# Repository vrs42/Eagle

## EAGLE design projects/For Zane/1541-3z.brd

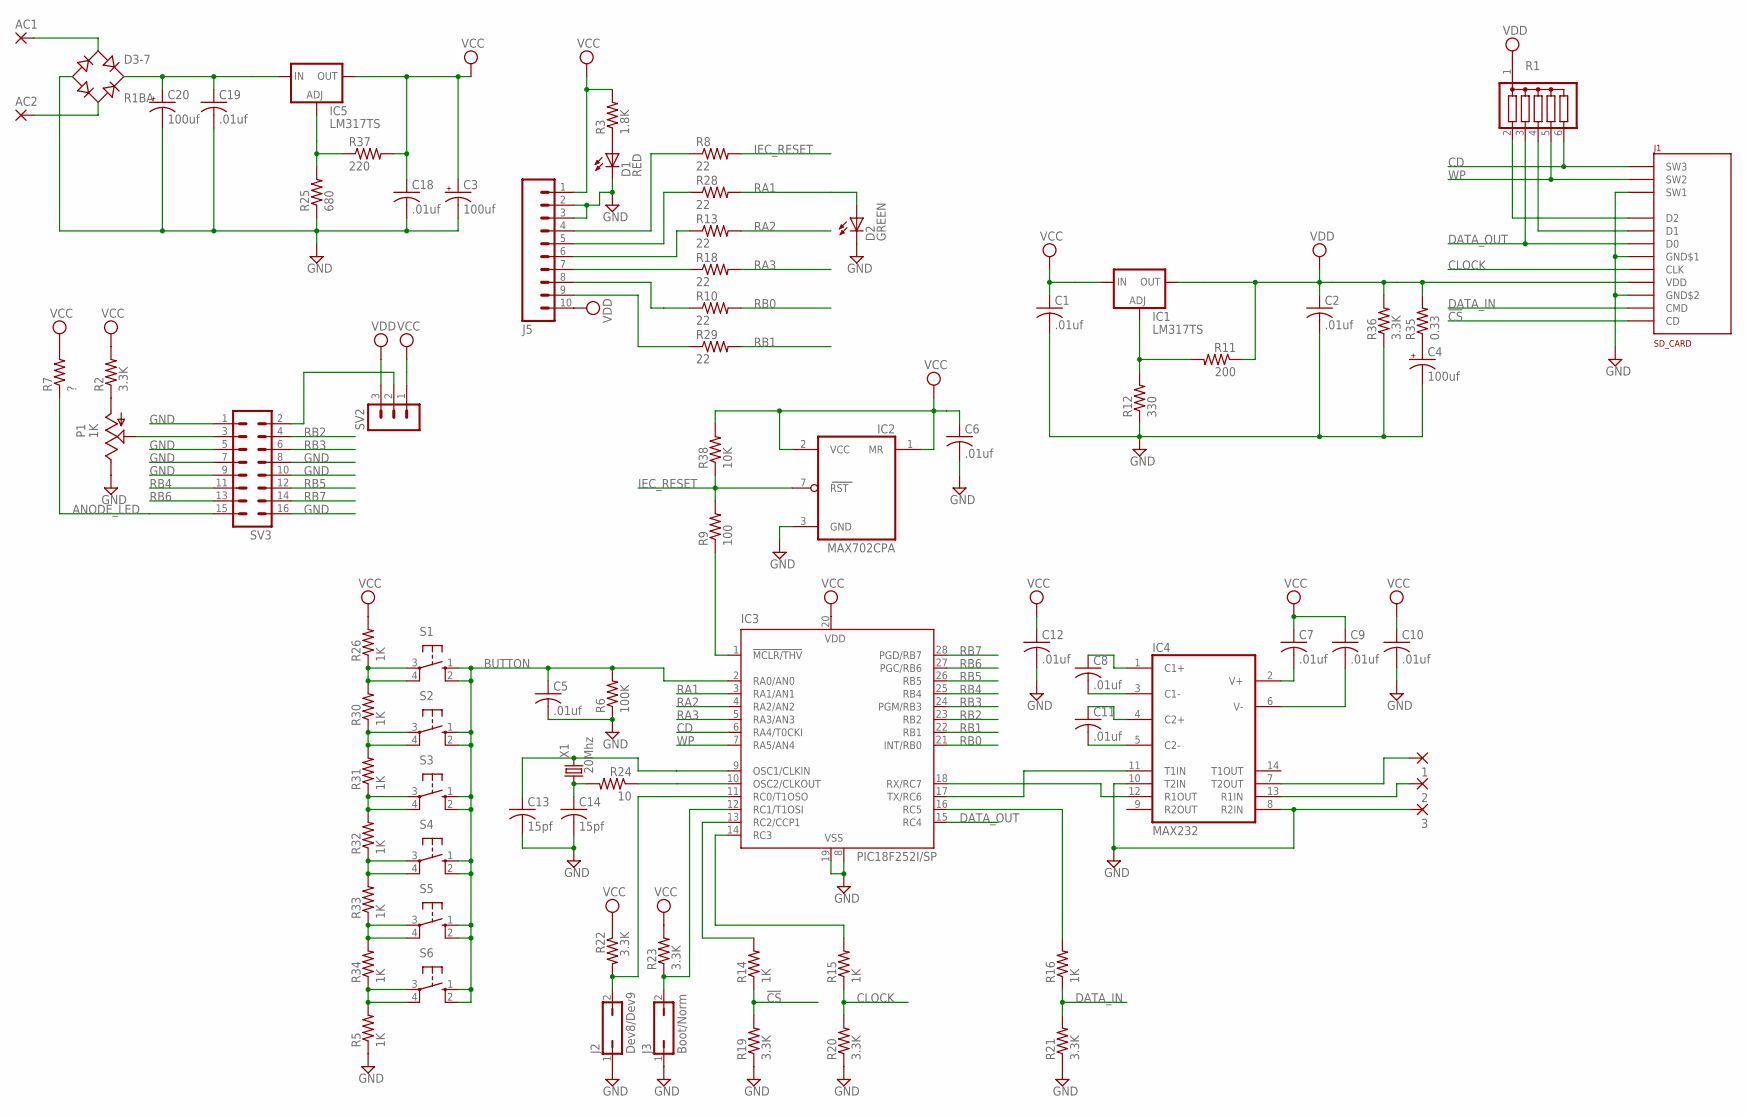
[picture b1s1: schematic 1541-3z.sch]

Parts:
1, 2, 3: 2,15/1,0
AC1, AC2: 2,15/1,0
C1, C2, C5, C6, C7, C8, C9, C10, C11, C12, C18, C19: .01uf; C025-024X044
C3, C4, C20: 100uf; E2-5
C13, C14: 15pf; C025-024X044
D1: RED; LED3MM
D2: GREEN; LED3MM
D3-7: R1BA; RB1A
IC1, IC5: LM317TS; 317TS
IC2: MAX702CPA; DIL08
IC3: PIC18F252I/SP; DIL28-3
IC4: MAX232; DIL16
J1: SD_CARD
J2: Dev8/Dev9; JP1
J3: Boot/Norm; JP1
J5: M10; 10P
P1: 1K; LI10
R1: G05R; SIL6
R2, R19, R20, R21, R22, R23, R36: 3.3K; 0207/2V
R3: 1.8K; 0207/2V
R5, R14, R15, R16, R26, R30, R31, R32, R33, R34: 1K; 0207/2V
R6: 100K; 0207/2V
R7: ?; 0207/2V
R8, R10, R13, R18, R28, R29: 22; 0207/2V
R9: 100; 0207/2V
R11: 200; 0207/2V
R12: 330; 0207/2V
R24: 10; 0207/2V
R25: 680; 0207/2V
R35: 0.33; 0207/2V
R37: 220; 0207/2V
R38: 10K; 0207/2V
S1, S2, S3, S4, S5, S6: 10-XX; B3F-10XX
SV2: MA03-1
SV3: ML16
X1: 20Mhz; HC49U70

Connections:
!CS: J1.DAT3 (CD), R14.1, R19.2
ANODE_LED: R7.1, SV3.15
BUTTON: C5.1, IC3.2 (RA0/AN0), R6.2, S1.1 (S), S1.2 (S1), S2.1 (S), S2.2 (S1), S3.1 (S), S3.2 (S1), S4.1 (S), S4.2 (S1), S5.1 (S), S5.2 (S1), S6.1 (S), S6.2 (S1)
CD: IC3.6 (RA4/T0CKI), J1.SW3, R1.6
CLOCK: J1.CLK, R15.1, R20.2
DATA_IN: J1.CMD, R16.1, R21.2
DATA_OUT: IC3.15 (RC4), J1.DAT0 (D0), R1.3
GND: 3.1, C1.2, C2.2, C3.-, C4.-, C5.2, C6.2, C10.2, C12.2, C13.2, C14.2, C18.2, C19.2, C20.-, D1.K (C), D2.K (C), D3-7.-, IC2.3 (GND), IC3.8 (VSS), IC3.19 (VSS), IC4.8 (R2IN), IC4.10 (T2IN), IC4.15 (GND), J1.SW1, J1.VSS$1 (GND$1), J1.VSS$2 (GND$2), J2.1, J3.1, J5.2, J5.3, P1.E, R5.1, R6.1, R12.1, R19.1, R20.1, R21.1, R25.1, R36.1, SV3.1, SV3.5, SV3.7, SV3.8, SV3.9, SV3.10, SV3.16
IEC_RESET: IC2.7 (RST), R8.2, R9.2, R38.1
unnamed: C4.+, R35.1
unnamed: J1.DAT2 (D2), R1.2
unnamed: J1.DAT1 (D1), R1.4
unnamed: J5.9, R29.1
unnamed: J5.8, R10.1
unnamed: J5.7, R18.1
unnamed: J5.4, R8.1
unnamed: J5.5, R28.1
unnamed: J5.6, R13.1
unnamed: D1.A, R3.1
unnamed: IC3.18 (RX/RC7), IC4.12 (R1OUT)
unnamed: IC3.14 (RC3), R15.2
unnamed: C14.1, R24.2, X1.1
unnamed: IC3.1 (!MCLR/THV), R9.1
unnamed: C11.1, IC4.4 (C2+)
unnamed: C11.2, IC4.5 (C2-)
unnamed: C8.2, IC4.3 (C1-)
unnamed: C8.1, IC4.1 (C1+)
unnamed: C7.2, IC4.2 (V+)
unnamed: C13.1, IC3.9 (OSC1/CLKIN), X1.2
unnamed: IC3.10 (OSC2/CLKOUT), R24.1
unnamed: IC3.12 (RC1/T1OSI), J3.2, R23.1
unnamed: IC3.11 (RC0/T1OSO), J2.2, R22.2
unnamed: IC3.13 (RC2/CCP1), R14.2
unnamed: IC3.16 (RC5), R16.2
unnamed: IC1.1 (ADJ), R11.2, R12.2
unnamed: IC3.17 (TX/RC6), IC4.11 (T1IN)
unnamed: R26.1, R30.2, S1.3, S1.4 (P1)
unnamed: R30.1, R31.2, S2.3, S2.4 (P1)
unnamed: R31.1, R32.2, S3.3, S3.4 (P1)
unnamed: R5.2, R34.1, S6.3, S6.4 (P1)
unnamed: R33.1, R34.2, S5.3, S5.4 (P1)
unnamed: R32.1, R33.2, S4.3, S4.4 (P1)
unnamed: P1.A, R2.1
unnamed: SV2.2, SV3.2
unnamed: P1.S, SV3.3
unnamed: C9.2, IC4.6 (V-)
unnamed: IC5.1 (ADJ), R25.2, R37.1
unnamed: AC1.1, D3-7.AC1
unnamed: C19.1, C20.+, D3-7.+, IC5.3 (IN)
unnamed: AC2.1, D3-7.AC2
unnamed: 2.1, IC4.13 (R1IN)
unnamed: 1.1, IC4.7 (T2OUT)
RA1: D2.A, IC3.3 (RA1/AN1), R28.2
RA2: IC3.4 (RA2/AN2), R13.2
RA3: IC3.5 (RA3/AN3), R18.2
RB0: IC3.21 (INT/RB0), R10.2
RB1: IC3.22 (RB1), R29.2
RB2: IC3.23 (RB2), SV3.4
RB3: IC3.24 (PGM/RB3), SV3.6
RB4: IC3.25 (RB4), SV3.11
RB5: IC3.26 (RB5), SV3.12
RB6: IC3.27 (PGC/RB6), SV3.13
RB7: IC3.28 (PGD/RB7), SV3.14
VCC: C1.1, C3.+, C6.1, C7.1, C9.1, C10.1, C12.1, C18.1, IC1.3 (IN), IC2.1 (MR), IC2.2 (VCC), IC3.20 (VDD), IC4.16 (VCC), IC5.2 (OUT), J5.1, R2.2, R3.2, R7.2, R22.1, R23.2, R26.2, R37.2, R38.2, SV2.1
VDD: C2.1, IC1.2 (OUT), J1.VDD, J5.10, R1.1, R11.1, R35.2, R36.2, SV2.3
WP: IC3.7 (RA5/AN4), J1.SW2, R1.5

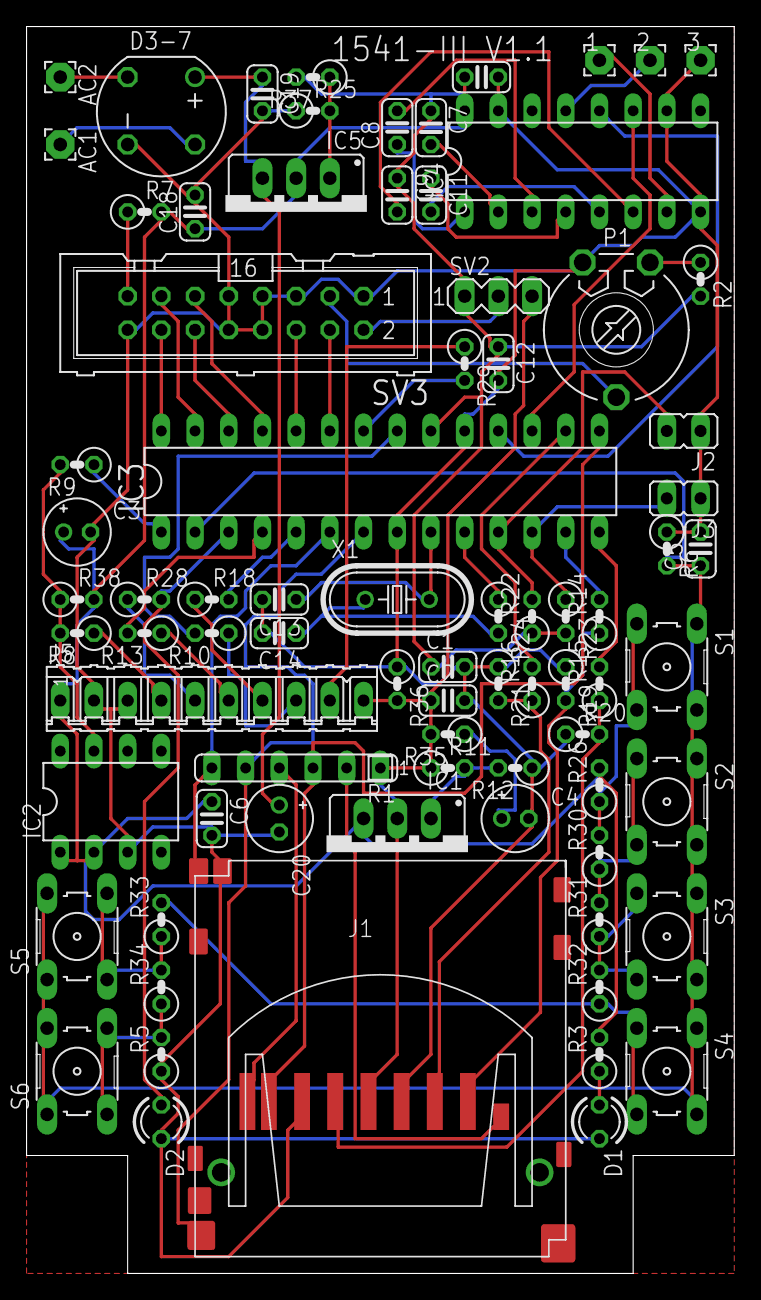
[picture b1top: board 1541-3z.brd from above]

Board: 2 copper layers, 53.3 x 94.0 mm, 79 parts (0 on the bottom side), 66 nets.

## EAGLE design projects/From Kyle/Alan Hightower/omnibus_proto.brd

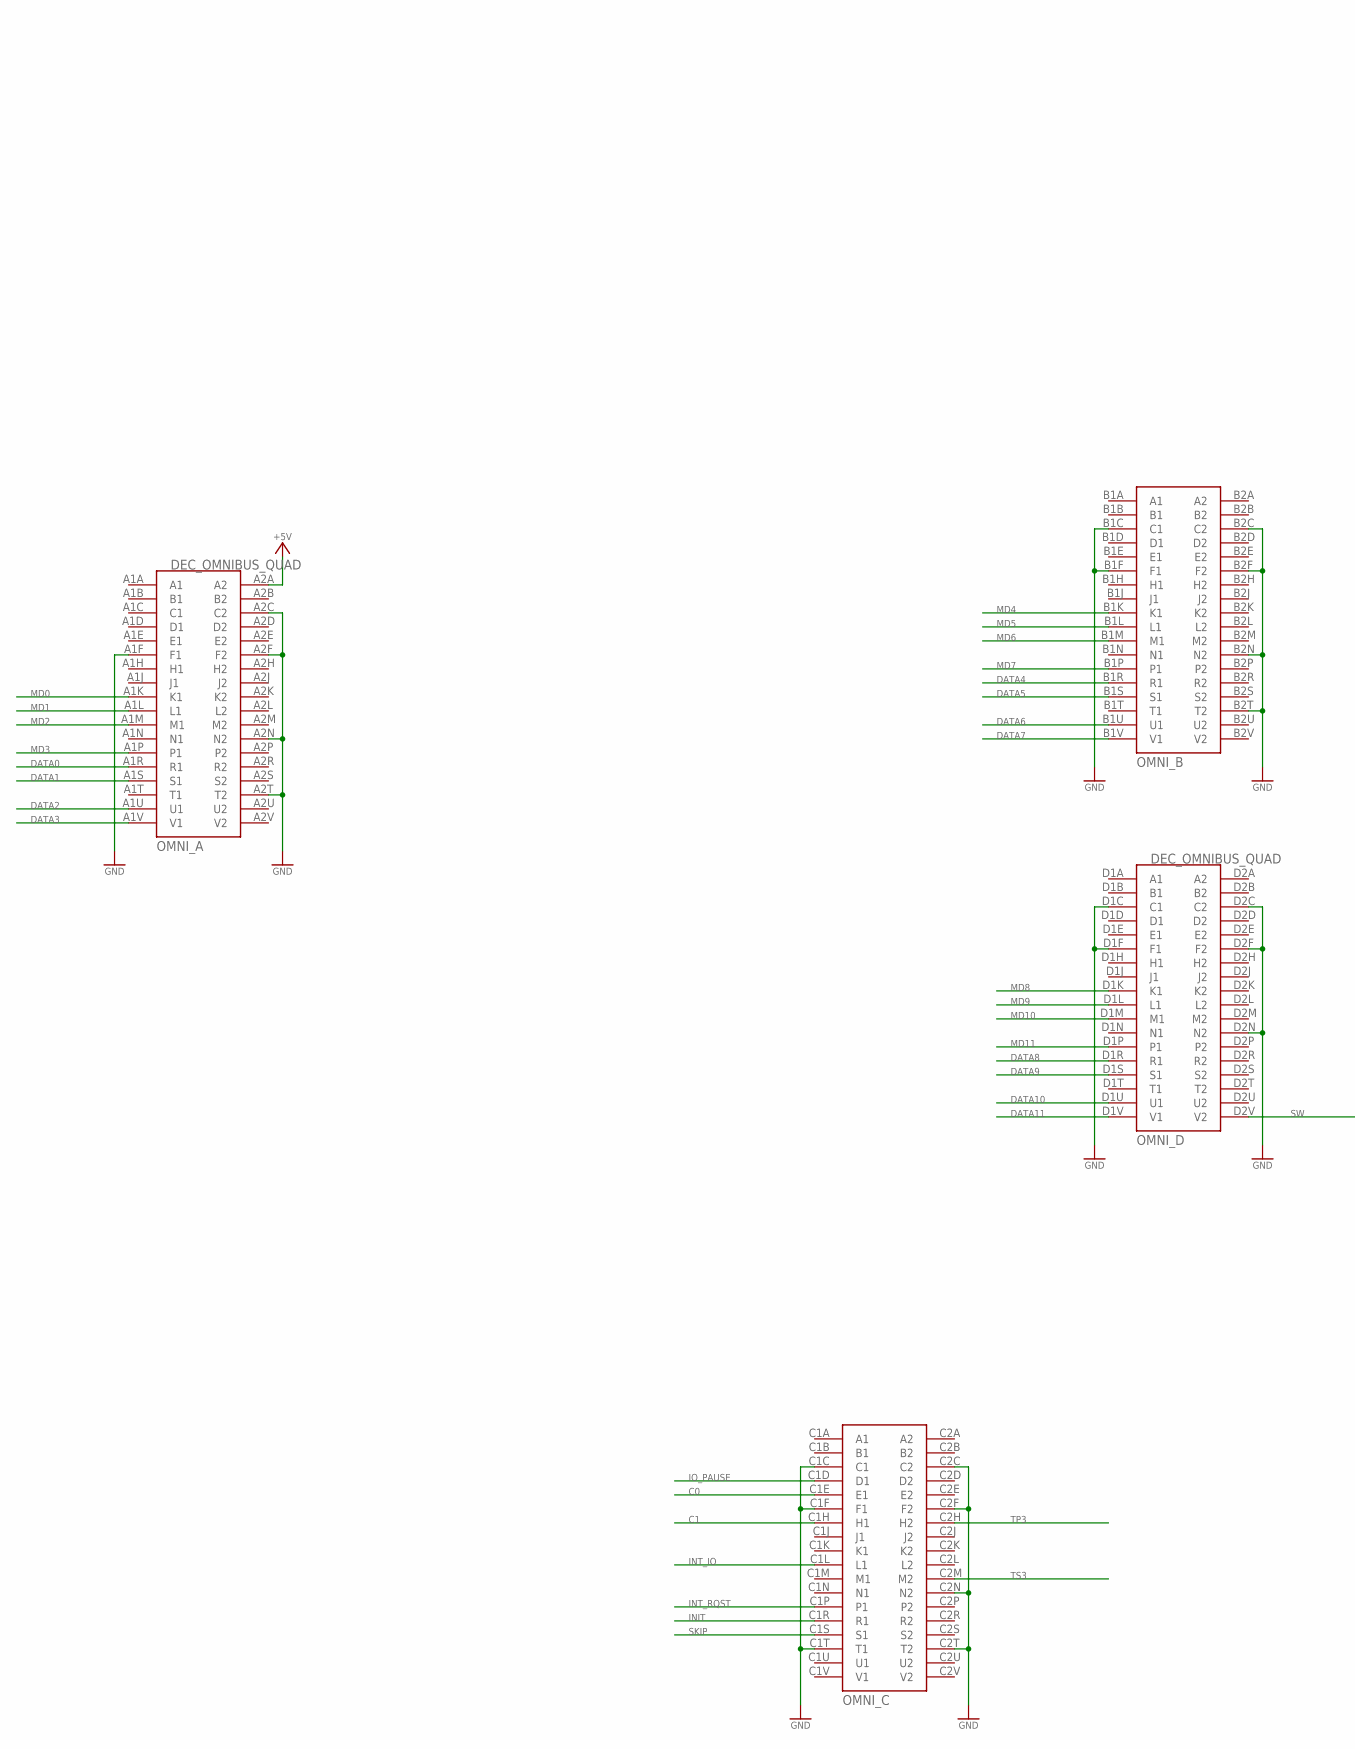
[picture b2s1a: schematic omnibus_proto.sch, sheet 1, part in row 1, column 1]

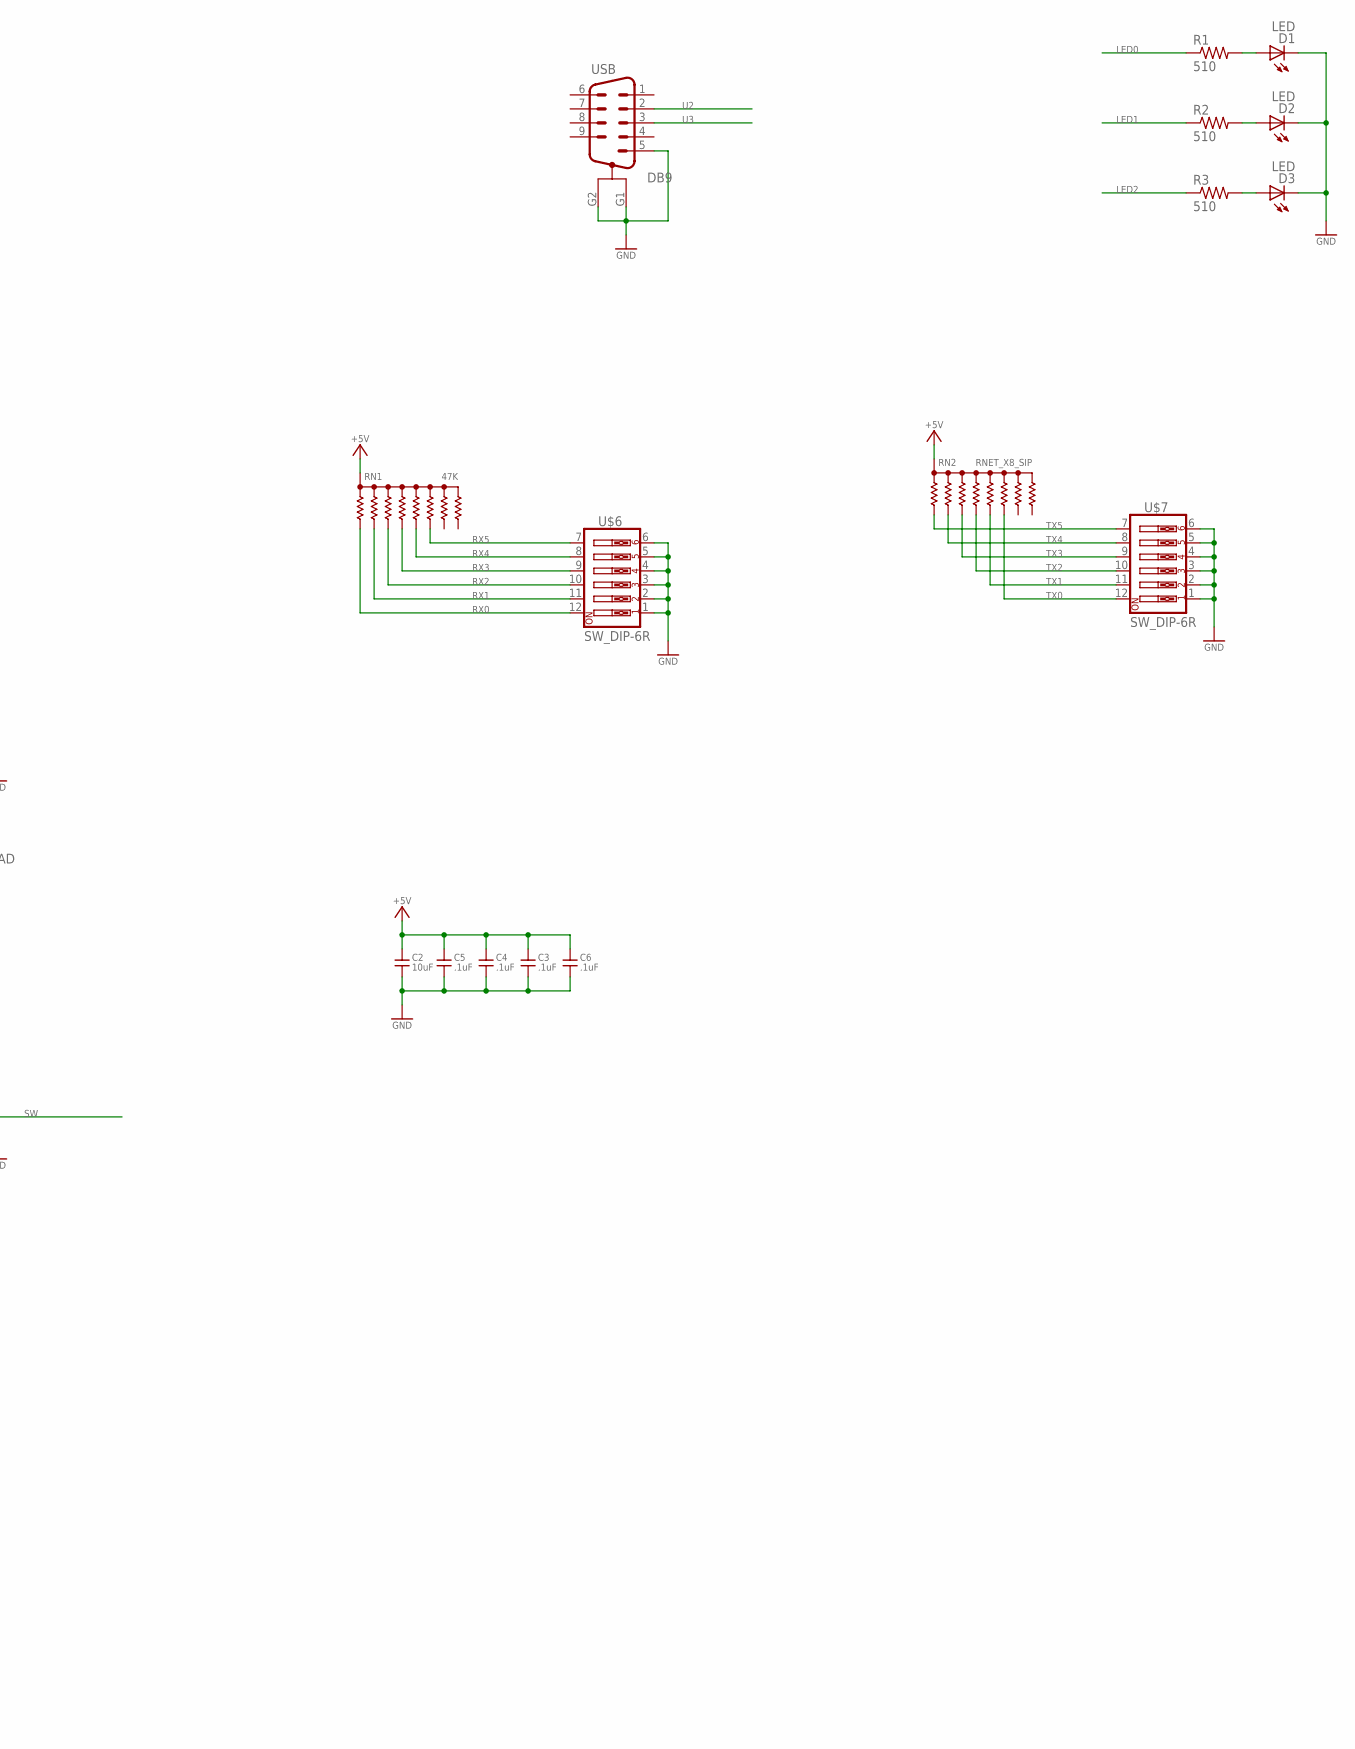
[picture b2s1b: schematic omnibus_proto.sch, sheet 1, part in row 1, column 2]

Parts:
C2: 10uF; C_TH_5MM
C3, C4, C5, C6: .1uF; C_TH_5MM
D1, D2, D3: LED; LED_TH_3MM
OMNI: DEC_OMNIBUS_QUAD
R1, R2, R3: 510; R_204/7
RN1: 47K; RN_SIP9
RN2: RNET_X8_SIP; RN_SIP9
U$6, U$7: SW_DIP-6R; SW_DIP-6_ROUND
USB: DB9; AMP_DB-9RA

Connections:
+5V: C2.1, C3.1, C4.1, C5.1, C6.1, OMNI.A2A (A2), RN1.1, RN2.1; also elsewhere on the board
C0: OMNI.C1E (E1); also elsewhere on the board
C1: OMNI.C1H (H1); also elsewhere on the board
DATA0: OMNI.A1R (R1); also elsewhere on the board
DATA1: OMNI.A1S (S1); also elsewhere on the board
DATA2: OMNI.A1U (U1); also elsewhere on the board
DATA3: OMNI.A1V (V1); also elsewhere on the board
DATA4: OMNI.B1R (R1); also elsewhere on the board
DATA5: OMNI.B1S (S1); also elsewhere on the board
DATA6: OMNI.B1U (U1); also elsewhere on the board
DATA7: OMNI.B1V (V1); also elsewhere on the board
DATA8: OMNI.D1R (R1); also elsewhere on the board
DATA9: OMNI.D1S (S1); also elsewhere on the board
DATA10: OMNI.D1U (U1); also elsewhere on the board
DATA11: OMNI.D1V (V1); also elsewhere on the board
GND: C2.2, C3.2, C4.2, C5.2, C6.2, D1.K (C), D2.K (C), D3.K (C), OMNI.A1F (F1), OMNI.A2C (C2), OMNI.A2F (F2), OMNI.A2N (N2), OMNI.A2T (T2), OMNI.B1C (C1), OMNI.B1F (F1), OMNI.B2C (C2), OMNI.B2F (F2), OMNI.B2N (N2), OMNI.B2T (T2), OMNI.C1C (C1), OMNI.C1F (F1), OMNI.C1T (T1), OMNI.C2C (C2), OMNI.C2F (F2), OMNI.C2N (N2), OMNI.C2T (T2), OMNI.D1C (C1), OMNI.D1F (F1), OMNI.D2C (C2), OMNI.D2F (F2), OMNI.D2N (N2), U$6.1, U$6.2, U$6.3, U$6.4, U$6.5, U$6.6, U$7.1, U$7.2, U$7.3, U$7.4, U$7.5, U$7.6, USB.5, USB.G1, USB.G2; also elsewhere on the board
INIT: OMNI.C1R (R1); also elsewhere on the board
INT_IO: OMNI.C1L (L1); also elsewhere on the board
INT_RQST: OMNI.C1P (P1); also elsewhere on the board
IO_PAUSE: OMNI.C1D (D1); also elsewhere on the board
LED0: R1.1; also elsewhere on the board
LED1: R2.1; also elsewhere on the board
LED2: R3.1; also elsewhere on the board
MD0: OMNI.A1K (K1); also elsewhere on the board
MD1: OMNI.A1L (L1); also elsewhere on the board
MD2: OMNI.A1M (M1); also elsewhere on the board
MD3: OMNI.A1P (P1); also elsewhere on the board
MD4: OMNI.B1K (K1); also elsewhere on the board
MD5: OMNI.B1L (L1); also elsewhere on the board
MD6: OMNI.B1M (M1); also elsewhere on the board
MD7: OMNI.B1P (P1); also elsewhere on the board
MD8: OMNI.D1K (K1); also elsewhere on the board
MD9: OMNI.D1L (L1); also elsewhere on the board
MD10: OMNI.D1M (M1); also elsewhere on the board
MD11: OMNI.D1P (P1); also elsewhere on the board
unnamed: D3.A, R3.2
unnamed: D2.A, R2.2
unnamed: D1.A, R1.2
RX0: RN1.2, U$6.12; also elsewhere on the board
RX1: RN1.3, U$6.11; also elsewhere on the board
RX2: RN1.4, U$6.10; also elsewhere on the board
RX3: RN1.5, U$6.9; also elsewhere on the board
RX4: RN1.6, U$6.8; also elsewhere on the board
RX5: RN1.7, U$6.7; also elsewhere on the board
SKIP: OMNI.C1S (S1); also elsewhere on the board
SW: OMNI.D2V (V2); also elsewhere on the board
TP3: OMNI.C2H (H2); also elsewhere on the board
TS3: OMNI.C2M (M2); also elsewhere on the board
TX0: RN2.7, U$7.12; also elsewhere on the board
TX1: RN2.6, U$7.11; also elsewhere on the board
TX2: RN2.5, U$7.10; also elsewhere on the board
TX3: RN2.4, U$7.9; also elsewhere on the board
TX4: RN2.3, U$7.8; also elsewhere on the board
TX5: RN2.2, U$7.7; also elsewhere on the board
U2: USB.2; also elsewhere on the board
U3: USB.3; also elsewhere on the board

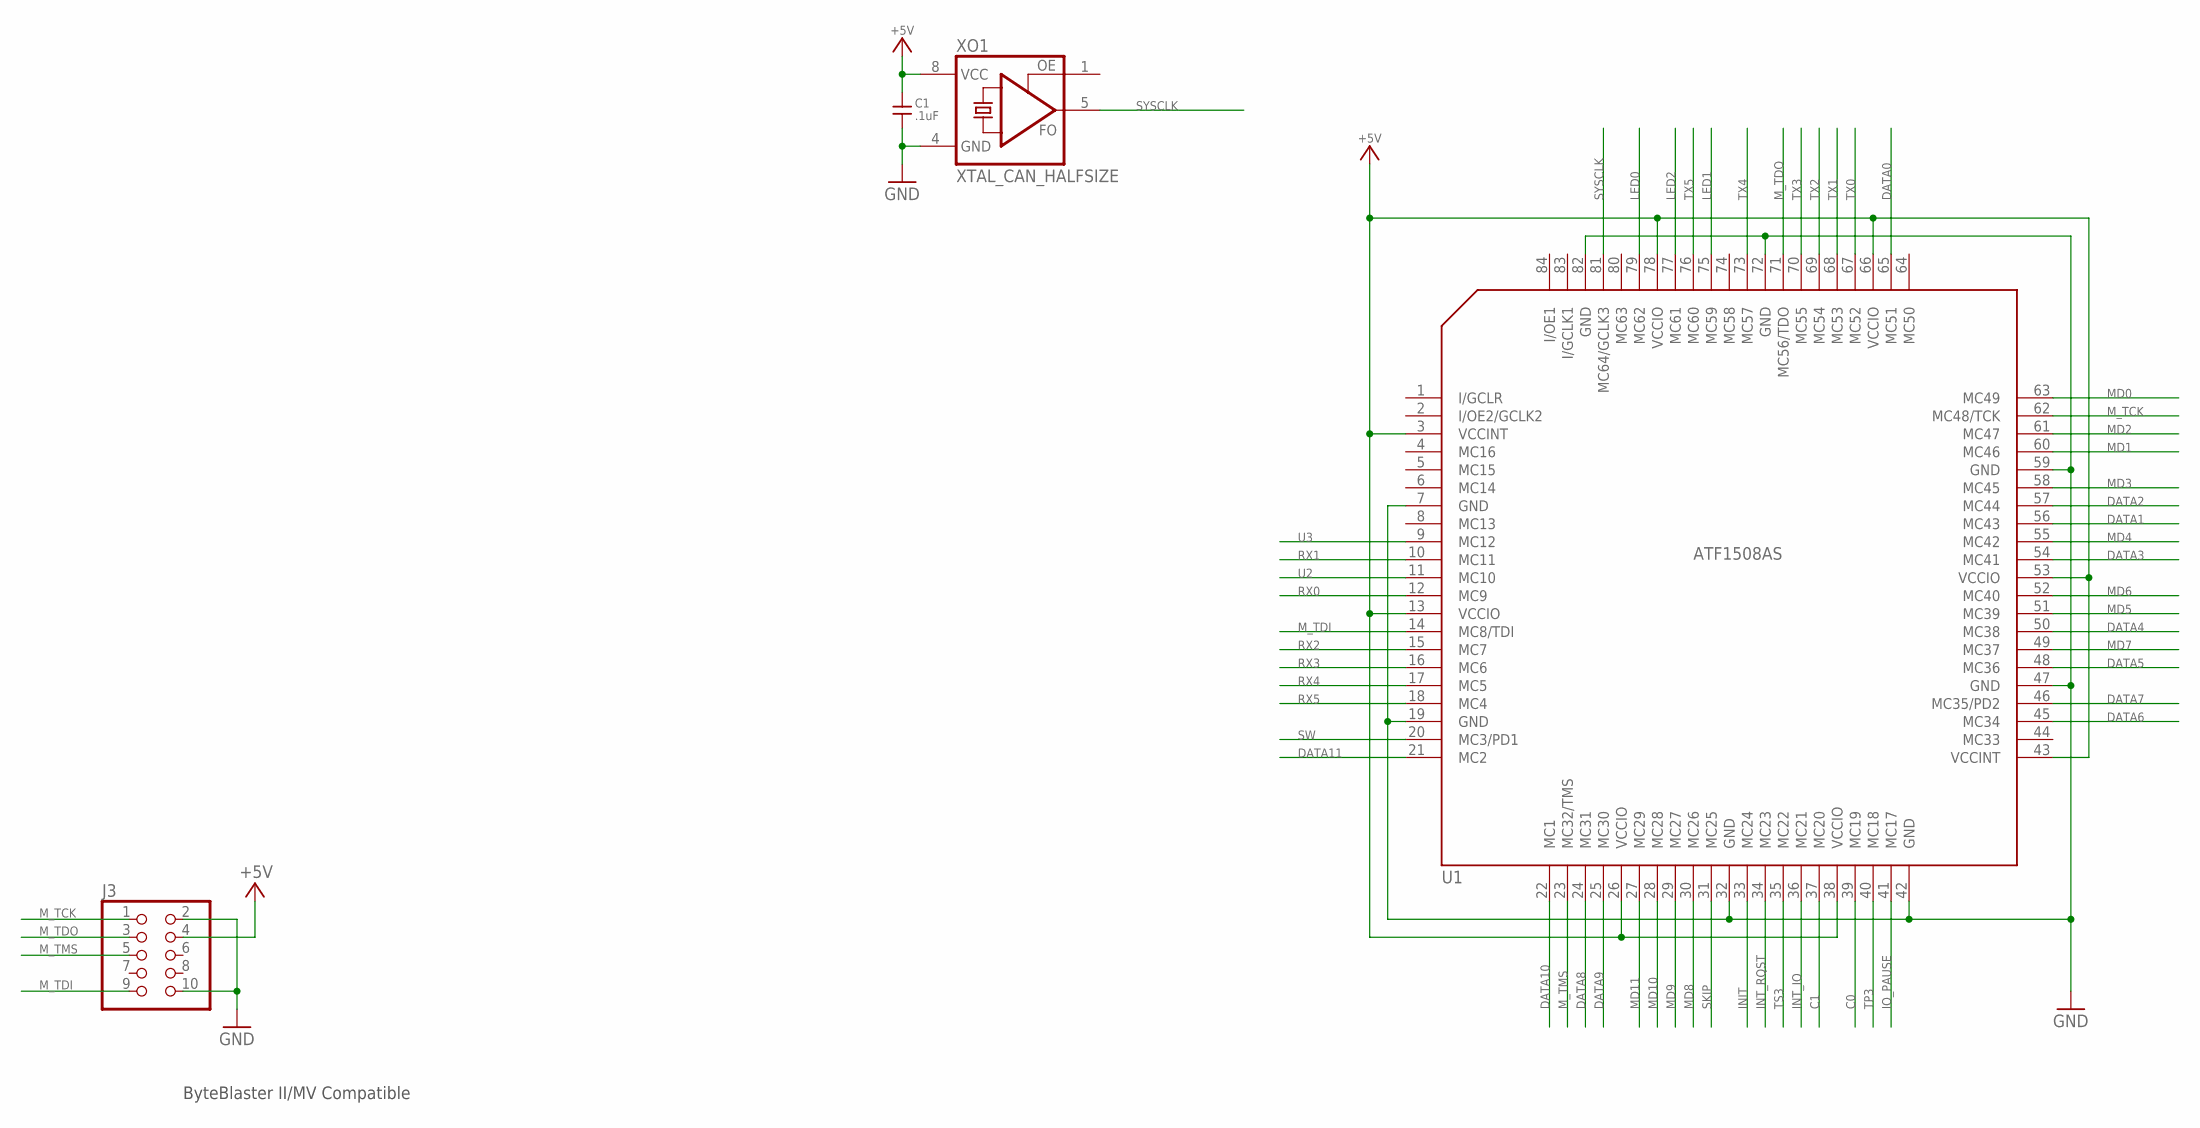
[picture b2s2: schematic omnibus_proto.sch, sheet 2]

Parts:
C1: .1uF; C_TH_5MM
J3: HDR_2X5"; HDR_2X5
U1: ATF1508AS; PLCC84
XO1: XTAL_CAN_HALFSIZE

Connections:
+5V: C1.1, J3.4, U1.3 (VCCINT), U1.13 (VCCIO), U1.26 (VCCIO), U1.38 (VCCIO), U1.43 (VCCINT), U1.53 (VCCIO), U1.66 (VCCIO), U1.78 (VCCIO), XO1.8 (VCC); also elsewhere on the board
C0: U1.39 (MC19); also elsewhere on the board
C1: U1.37 (MC20); also elsewhere on the board
DATA0: U1.65 (MC51); also elsewhere on the board
DATA1: U1.56 (MC43); also elsewhere on the board
DATA2: U1.57 (MC44); also elsewhere on the board
DATA3: U1.54 (MC41); also elsewhere on the board
DATA4: U1.50 (MC38); also elsewhere on the board
DATA5: U1.48 (MC36); also elsewhere on the board
DATA6: U1.45 (MC34); also elsewhere on the board
DATA7: U1.46 (MC35/PD2); also elsewhere on the board
DATA8: U1.24 (MC31); also elsewhere on the board
DATA9: U1.25 (MC30); also elsewhere on the board
DATA10: U1.22 (MC1); also elsewhere on the board
DATA11: U1.21 (MC2); also elsewhere on the board
GND: C1.2, J3.2, J3.10, U1.7 (GND), U1.19 (GND), U1.32 (GND), U1.42 (GND), U1.47 (GND), U1.59 (GND), U1.72 (GND), U1.82 (GND), XO1.4 (GND); also elsewhere on the board
INIT: U1.33 (MC24); also elsewhere on the board
INT_IO: U1.36 (MC21); also elsewhere on the board
INT_RQST: U1.34 (MC23); also elsewhere on the board
IO_PAUSE: U1.41 (MC17); also elsewhere on the board
LED0: U1.79 (MC62); also elsewhere on the board
LED1: U1.75 (MC59); also elsewhere on the board
LED2: U1.77 (MC61); also elsewhere on the board
MD0: U1.63 (MC49); also elsewhere on the board
MD1: U1.60 (MC46); also elsewhere on the board
MD2: U1.61 (MC47); also elsewhere on the board
MD3: U1.58 (MC45); also elsewhere on the board
MD4: U1.55 (MC42); also elsewhere on the board
MD5: U1.51 (MC39); also elsewhere on the board
MD6: U1.52 (MC40); also elsewhere on the board
MD7: U1.49 (MC37); also elsewhere on the board
MD8: U1.30 (MC26); also elsewhere on the board
MD9: U1.29 (MC27); also elsewhere on the board
MD10: U1.28 (MC28); also elsewhere on the board
MD11: U1.27 (MC29); also elsewhere on the board
M_TCK: J3.1, U1.62 (MC48/TCK)
M_TDI: J3.9, U1.14 (MC8/TDI)
M_TDO: J3.3, U1.71 (MC56/TDO)
M_TMS: J3.5, U1.23 (MC32/TMS)
RX0: U1.12 (MC9); also elsewhere on the board
RX1: U1.10 (MC11); also elsewhere on the board
RX2: U1.15 (MC7); also elsewhere on the board
RX3: U1.16 (MC6); also elsewhere on the board
RX4: U1.17 (MC5); also elsewhere on the board
RX5: U1.18 (MC4); also elsewhere on the board
SKIP: U1.31 (MC25); also elsewhere on the board
SW: U1.20 (MC3/PD1); also elsewhere on the board
SYSCLK: U1.81 (MC64/GCLK3), XO1.5 (FO)
TP3: U1.40 (MC18); also elsewhere on the board
TS3: U1.35 (MC22); also elsewhere on the board
TX0: U1.67 (MC52); also elsewhere on the board
TX1: U1.68 (MC53); also elsewhere on the board
TX2: U1.69 (MC54); also elsewhere on the board
TX3: U1.70 (MC55); also elsewhere on the board
TX4: U1.73 (MC57); also elsewhere on the board
TX5: U1.76 (MC60); also elsewhere on the board
U2: U1.11 (MC10); also elsewhere on the board
U3: U1.9 (MC12); also elsewhere on the board

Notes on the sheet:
ByteBlaster II/MV Compatible

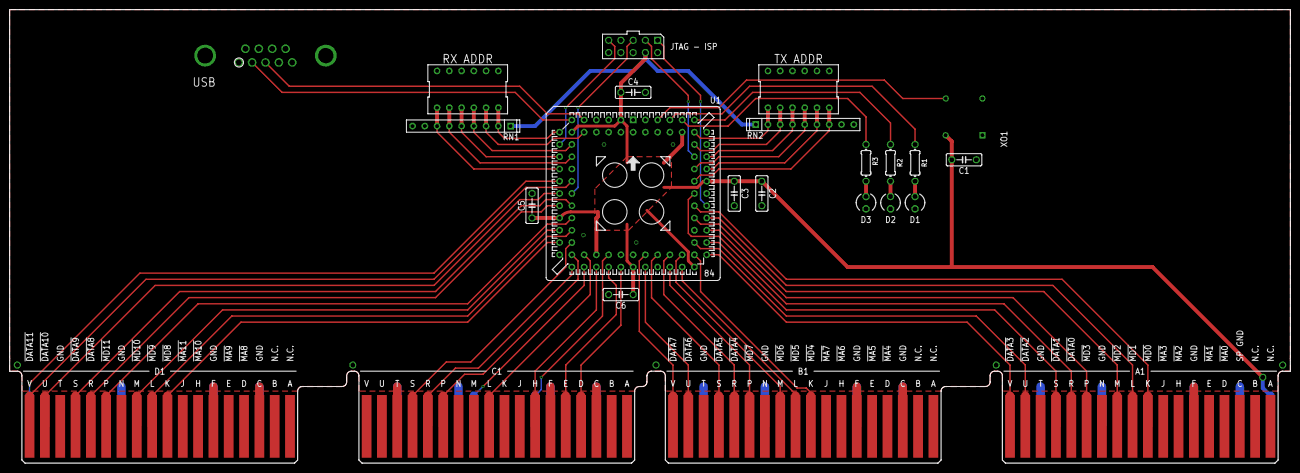
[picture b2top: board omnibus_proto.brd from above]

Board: 2 copper layers, 265.4 x 94.0 mm, 21 parts (0 on the bottom side), 61 nets.

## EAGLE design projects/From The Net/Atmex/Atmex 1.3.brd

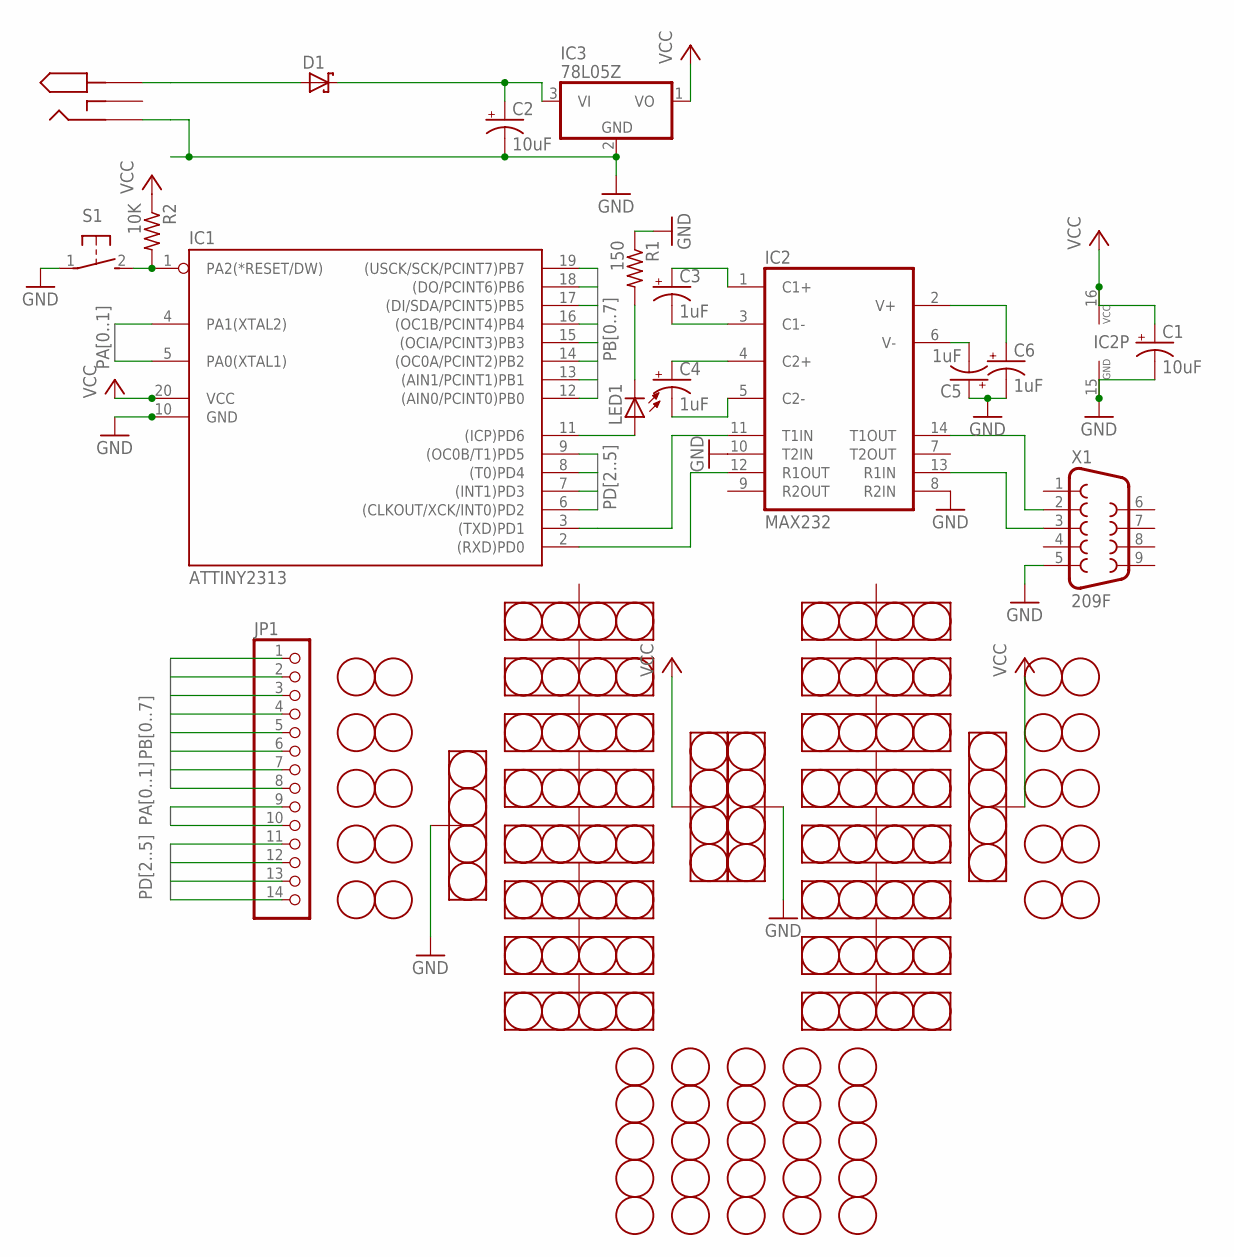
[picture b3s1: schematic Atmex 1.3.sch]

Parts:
C1, C2: 10uF; E2-5
C3, C4, C5, C6: 1uF; E1,8-4
D1: SCHOTTKY-DIODEDO35-7; DO35-7
IC1: ATTINY2313; DIL20
IC2: MAX232; DIL16
IC3: 78L05Z; TO92
JP1: PINHD-1X14; 1X14
LED1: LED5MM
R1: 150; 0204/7
R2: 10K; 0204/7
S1: 31-XX; B3F-31XX
U$1: 2.1MMJACK; PJ-102A
U$2, U$3, U$4, U$5, U$6, U$7, U$8, U$9, U$10, U$11, U$14, U$15, U$18, U$19, U$23, U$24: PROTOAREAPROTO3; PROTO_3
U$12, U$13, U$25, U$26: HEADER12; HEADER_12
U$16, U$17: PROTOAREA; PROTO_12
U$21, U$22: PROTOAREAPROTO8; PROTO_8
U$27: HEADER14; HEADER_14
U$28, U$29, U$30, U$31: HEADER8; HEADER_8
X1: 209F; F09D

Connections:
GND: C1.-, C2.-, C5.+, C6.-, IC1.10 (GND), IC2.8 (R2IN), IC2.10 (T2IN), IC2.15 (GND), IC3.2 (GND), R1.1, S1.1, U$1.R, U$16.P$1, U$22.P$1, X1.5
unnamed: C3.-, IC2.3 (C1-)
unnamed: C3.+, IC2.1 (C1+)
unnamed: C4.+, IC2.4 (C2+)
unnamed: C4.-, IC2.5 (C2-)
unnamed: IC1.1 (PA2(*RESET/DW)), R2.2, S1.2 (S)
unnamed: C2.+, D1.C, IC3.3 (VI)
unnamed: C5.-, IC2.6 (V-)
unnamed: IC2.13 (R1IN), X1.3
unnamed: C6.+, IC2.2 (V+)
unnamed: IC2.14 (T1OUT), X1.2
unnamed: IC1.11 ((ICP)PD6), LED1.A
unnamed: LED1.K (C), R1.2
unnamed: D1.A, U$1.T
PA0: IC1.5 (PA0(XTAL1)), JP1.9
PA1: IC1.4 (PA1(XTAL2)), JP1.10
PB0: IC1.12 ((AIN0/PCINT0)PB0), JP1.1
PB1: IC1.13 ((AIN1/PCINT1)PB1), JP1.2
PB2: IC1.14 ((OC0A/PCINT2)PB2), JP1.3
PB3: IC1.15 ((OCIA/PCINT3)PB3), JP1.4
PB4: IC1.16 ((OC1B/PCINT4)PB4), JP1.5
PB5: IC1.17 ((DI/SDA/PCINT5)PB5), JP1.6
PB6: IC1.18 ((DO/PCINT6)PB6), JP1.7
PB7: IC1.19 ((USCK/SCK/PCINT7)PB7), JP1.8
PD0: IC1.2 ((RXD)PD0), IC2.12 (R1OUT)
PD1: IC1.3 ((TXD)PD1), IC2.11 (T1IN)
PD2: IC1.6 ((CLKOUT/XCK/INT0)PD2), JP1.11
PD3: IC1.7 ((INT1)PD3), JP1.12
PD4: IC1.8 ((T0)PD4), JP1.13
PD5: IC1.9 ((OC0B/T1)PD5), JP1.14
VCC: C1.+, IC1.20 (VCC), IC2.16 (VCC), IC3.1 (VO), R2.1, U$17.P$1, U$21.P$1

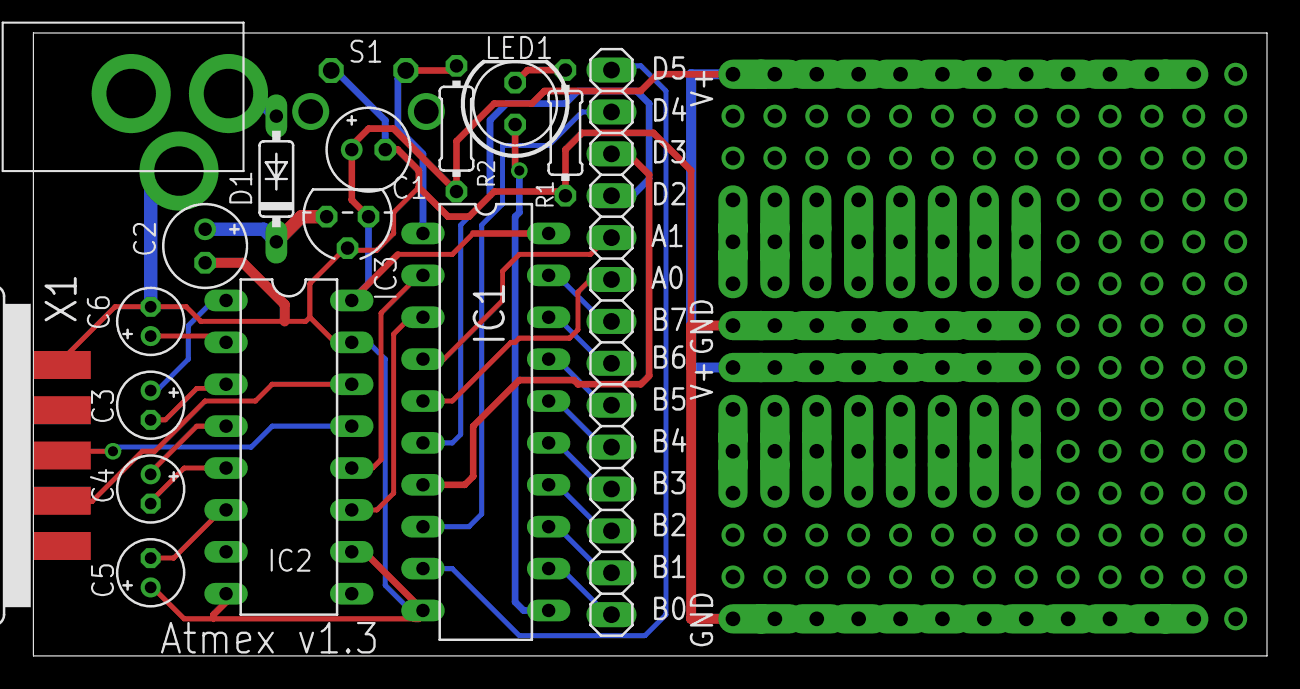
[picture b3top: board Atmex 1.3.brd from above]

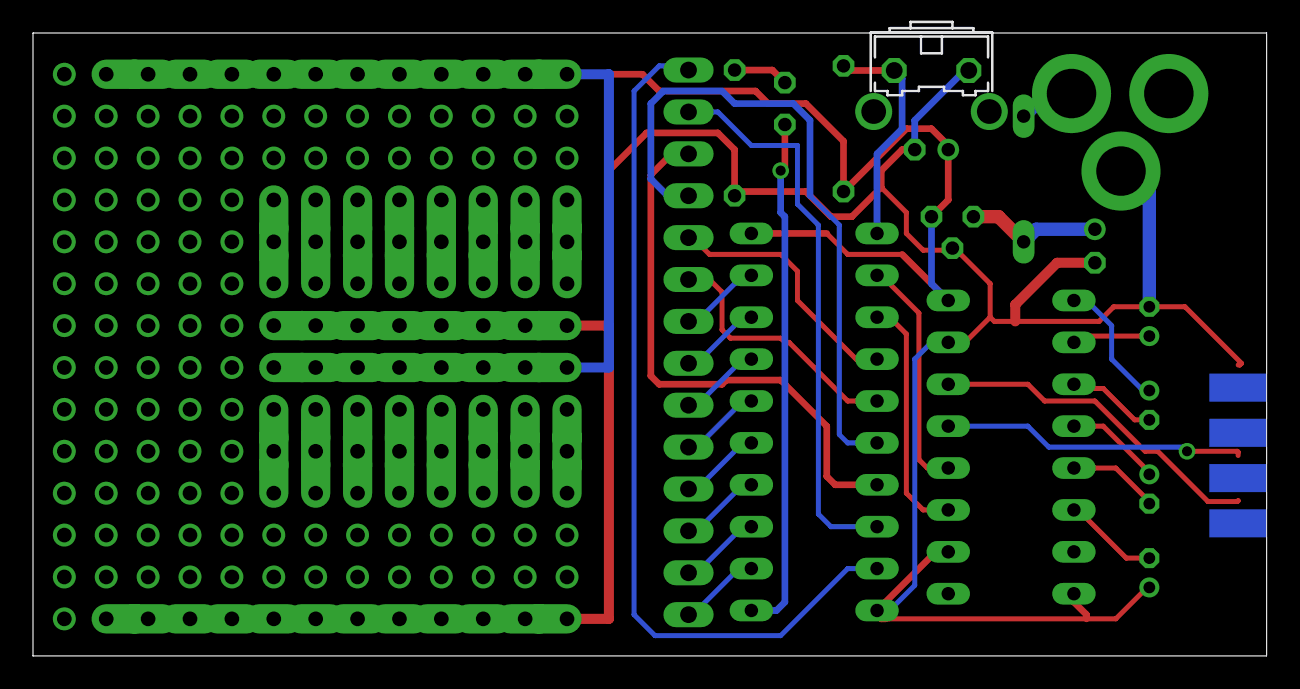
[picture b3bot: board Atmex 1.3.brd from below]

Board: 2 copper layers, 74.8 x 37.8 mm, 46 parts (30 on the bottom side), 31 nets.
